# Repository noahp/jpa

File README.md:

# JPA- *J*ST *P*rogramming *A*dapter
Little adapter board to connect standard PIC 6-pin or SWD 10-pin programming cables to Micro JST 1.0mm cables.
# 3D Render

# PCB Render

# Part reference
[6-pin jst header](http://www.aliexpress.com/item/SM06B-SRSS-TB-LF-SN-CONN-RCPT-SR-6-POS-1-0MM-TIN-JST-Connectors-SM06BSRSSTBLFSN/1156361078.html)  
[6-pin jst cable](http://www.aliexpress.com/item/Wholesale-100pcs-Micro-JST-SH-1-0mm-Pitch-6-Pin-Female-Connector-with-Wire-jst-6pin/32299265934.html?spm=2114.01020208.3.160.fzax0q&ws_ab_test=searchweb201556_4_79_78_77_92_91_80,searchweb201644_5,searchweb201560_9)  
[5-pin jst header](http://www.digikey.com/product-detail/en/SM05B-SRSS-TB(LF)(SN)/455-1805-1-ND/926876)  
[5-pin jst cable](http://www.aliexpress.com/item/10pcs-Micro-JST-1-0mm-5pin-Connector-plug-with-wire/32506663955.html)  
[10-pin header](http://www.digikey.com/product-detail/en/3220-10-0100-00/1175-1627-ND/3883661)  
[10-pin smt header](http://www.digikey.com/product-detail/en/3220-10-0300-00/1175-1629-ND/3883266)  
[6-pin 0.1" header](http://www.digikey.com/product-detail/en/SM06B-SRSS-TB(LF)(SN)/455-1806-1-ND/926877)

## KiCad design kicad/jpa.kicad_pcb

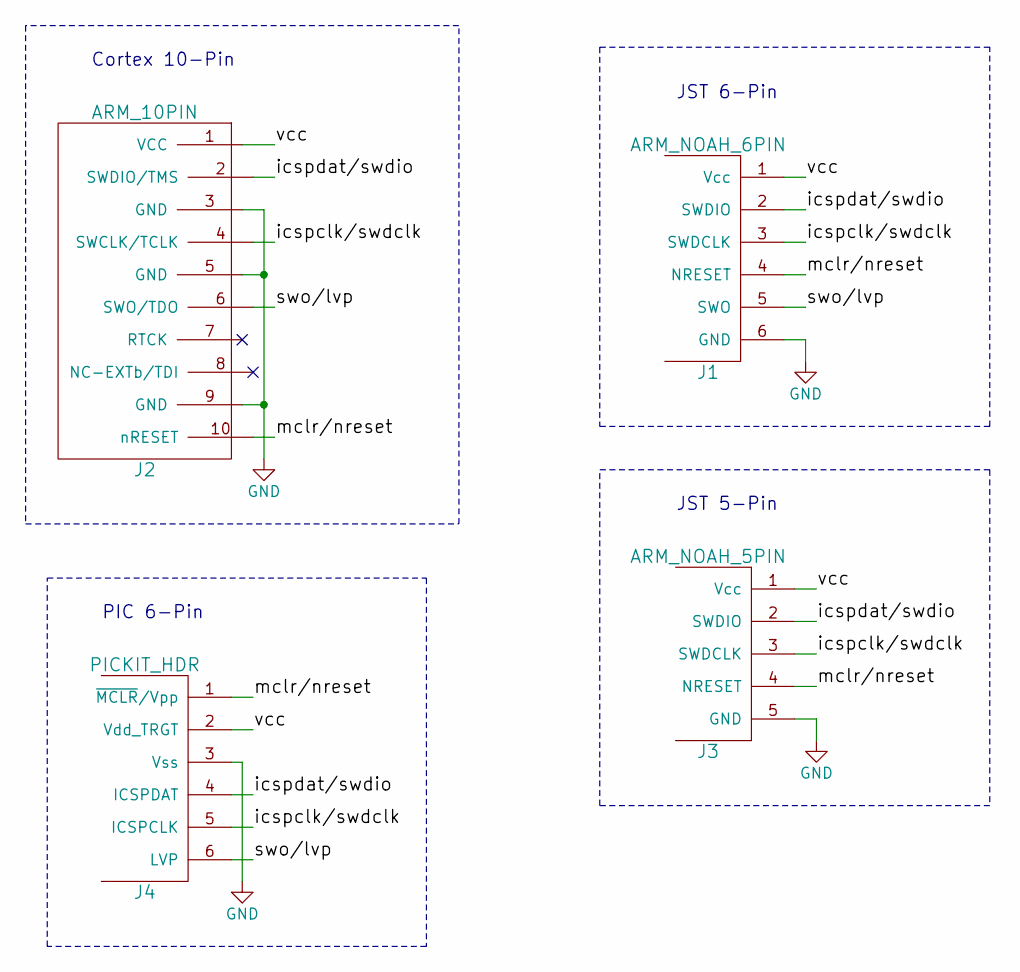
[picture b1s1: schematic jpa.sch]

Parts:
J1: ARM_NOAH_6PIN; SMD_JST_6_PIN_VERT
J2: ARM_10PIN; ARM_10_PIN
J3: ARM_NOAH_5PIN; SMD_JST_5_PIN_VERT
J4: PICKIT_HDR

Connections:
/icspclk/swdclk: J1.3 (SWDCLK), J2.4 (SWCLK/TCLK), J3.3 (SWDCLK), J4.5 (ICSPCLK)
/icspdat/swdio: J1.2 (SWDIO), J2.2 (SWDIO/TMS), J3.2 (SWDIO), J4.4 (ICSPDAT)
/mclr/nreset: J1.4 (NRESET), J2.10 (nRESET), J3.4 (NRESET), J4.1 (~MCLR~/Vpp)
/swo/lvp: J1.5 (SWO), J2.6 (SWO/TDO), J4.6 (LVP)
/vcc: J1.1 (Vcc), J2.1 (VCC), J3.1 (Vcc), J4.2 (Vdd_TRGT)
GND: J1.6 (GND), J2.3 (GND), J2.5 (GND), J2.9 (GND), J3.5 (GND), J4.3 (Vss)

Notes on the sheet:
Cortex 10-Pin
PIC 6-Pin
JST 6-Pin
JST 5-Pin

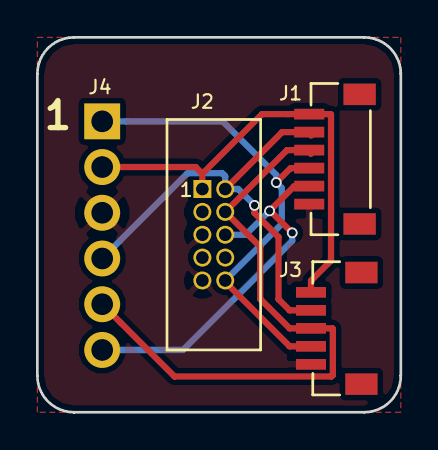
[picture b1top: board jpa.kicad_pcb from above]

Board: 2 copper layers, 20.2 x 20.8 mm, 4 parts (0 on the bottom side), 6 nets.

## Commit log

2015-11-03 add blank files
2015-11-03 add normal kicadlib
2015-11-03 usb Micro AB connector connected to 3 debug headers- arm 10pin, pic 6 pin, noah-arm 5pin (micro jst).
2015-11-04 rename!
2015-11-04 schematic done
2015-11-10 update arm 6-pin header
2015-11-10 place components, still need a footprint for pic connector
2015-11-11 layout, gerbers, models done
2015-11-11 add pcb renders
2015-11-11 fix some unconnected nets on the layout
2015-11-11 new renders, tighter layout (only saves ~0.60$ osh cost)
